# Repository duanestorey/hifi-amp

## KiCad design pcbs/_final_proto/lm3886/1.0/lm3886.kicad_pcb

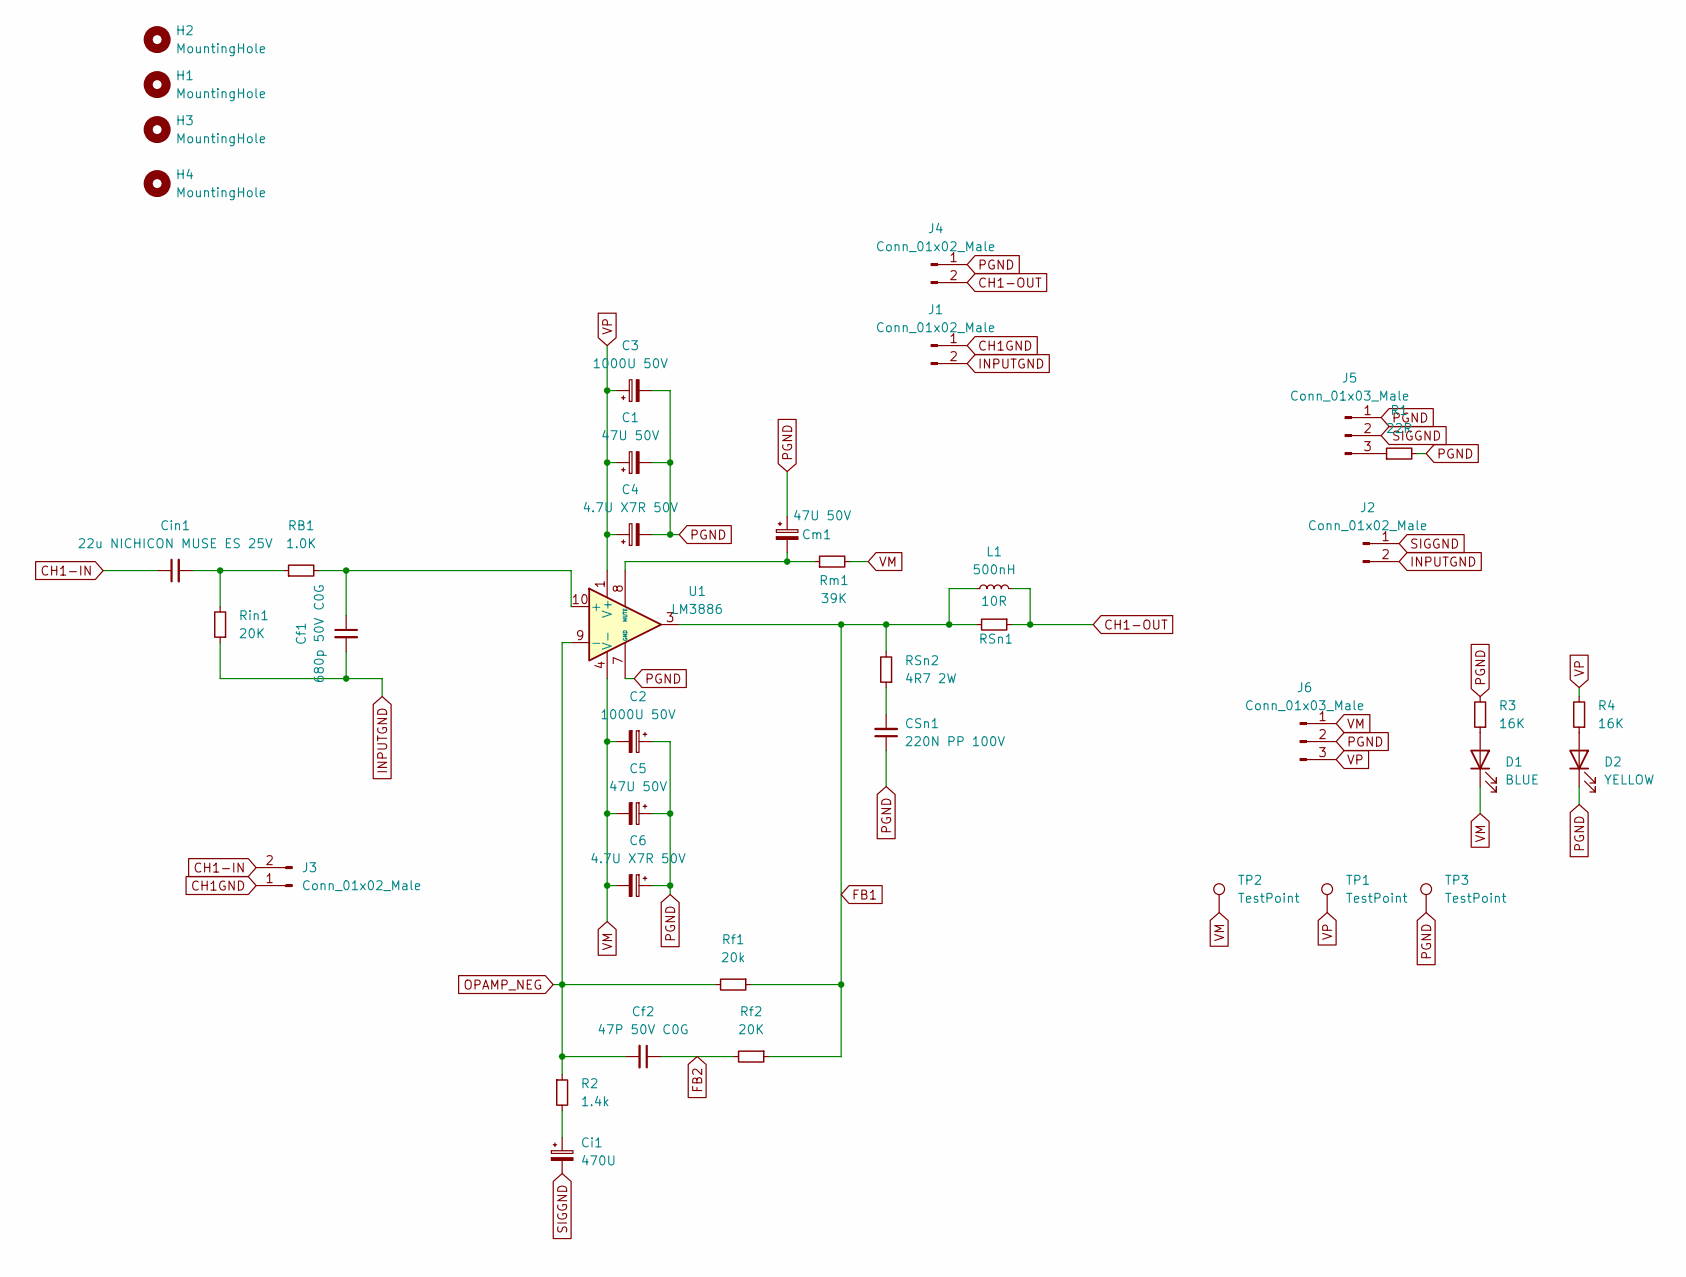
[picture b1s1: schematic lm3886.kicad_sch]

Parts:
C1, C5: 47U 50V; CP_Radial_D6.3mm_P2.50mm
C2, C3: 1000U 50V; CP_Radial_D12.5mm_P5.00mm
C4, C6: 4.7U X7R 50V; C_1206_3216Metric_Pad1.33x1.80mm_HandSolder; Mouser 80-C1206X475J5RACTU
CSn1: 220N PP 100V; C_Rect_L18.0mm_W7.0mm_P15.00mm_FKS3_FKP3; Mouser 505-MKP1D032204D00JB
Cf1: 680p 50V C0G; C_1206_3216Metric_Pad1.33x1.80mm_HandSolder; Mouser 603-CC126GRNPO9BN681
Cf2: 47P 50V C0G; C_1206_3216Metric_Pad1.33x1.80mm_HandSolder; Mouser 791-1206N470F500CT
Ci1: 470U; CP_Radial_D12.5mm_P5.00mm
Cin1: 22u NICHICON MUSE ES 25V; C_Radial_D6.3mm_H5.0mm_P2.50mm
Cm1: 47U 50V; CP_Radial_D6.3mm_P2.50mm
D1: BLUE; LED_0805_2012Metric_Pad1.15x1.40mm_HandSolder
D2: YELLOW; LED_0805_2012Metric_Pad1.15x1.40mm_HandSolder
H1, H2, H3, H4: MountingHole; MountingHole_3.2mm_M3_DIN965_Pad_TopOnly
J1, J2: Conn_01x02_Male; PinHeader_1x02_P2.54mm_Vertical
J3: Conn_01x02_Male; TerminalBlock_Phoenix_PT-1,5-2-3.5-H_1x02_P3.50mm_Horizontal
J4: Conn_01x02_Male; TerminalBlock_Phoenix_PT-1,5-2-5.0-H_1x02_P5.00mm_Horizontal
J5: Conn_01x03_Male; PinHeader_1x03_P2.54mm_Vertical
J6: Conn_01x03_Male; TerminalBlock_Phoenix_PT-1,5-3-5.0-H_1x03_P5.00mm_Horizontal
L1: 500nH; 500nH Inductor Aliexpress Air Gap
R1: 22R; R_1206_3216Metric_Pad1.30x1.75mm_HandSolder
R2: 1.4k; R_1206_3216Metric_Pad1.30x1.75mm_HandSolder; Mouser 603-RT1206FRE07750RL
R3, R4: 16K; R_0805_2012Metric_Pad1.20x1.40mm_HandSolder
RB1: 1.0K; R_1206_3216Metric_Pad1.30x1.75mm_HandSolder; Mouser 603-RT1206FRE131KL
RSn1: 10R; R_4020_10251Metric_Pad1.65x5.30mm_HandSolder; Mouser 279-355010RJT
RSn2: 4R7 2W; R_2512_6332Metric_Pad1.40x3.35mm_HandSolder; Mouser 603-RC2512JK-7W4R7
Rf1: 20k; R_1206_3216Metric_Pad1.30x1.75mm_HandSolder; Mouser 603-RT1206FRD0720KL
Rf2: 20K; R_1206_3216Metric_Pad1.30x1.75mm_HandSolder; Mouser 603-RT1206FRD0720KL
Rin1: 20K; R_1206_3216Metric_Pad1.30x1.75mm_HandSolder; Mouser 603-RT1206FRD0720KL
Rm1: 39K; R_1206_3216Metric_Pad1.30x1.75mm_HandSolder; Mouser 603-RC1206JR-0739KL
TP1, TP2, TP3: TestPoint; TestPoint_THTPad_1.5x1.5mm_Drill0.7mm
U1: LM3886; TO-220-11_P3.4x5.08mm_StaggerOdd_Lead4.85mm_Vertical

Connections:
CH1-IN: Cin1.1, J3.2
CH1-OUT: J4.2, L1.2, RSn1.1
CH1GND: J1.1, J3.1
FB1: L1.1, RSn1.2, RSn2.2, Rf1.1, Rf2.1, U1.3
FB2: Cf2.1, Rf2.2
INPUTGND: Cf1.2, J1.2, J2.2, Rin1.1
unnamed: CSn1.2, RSn2.1
unnamed: Ci1.1, R2.2
unnamed: Cin1.2, RB1.1, Rin1.2
unnamed: D1.2 (A), R3.1
unnamed: D2.2 (A), R4.1
unnamed: J5.3, R1.1
unnamed: Cf1.1, RB1.2, U1.10 (+)
unnamed: Cm1.2, Rm1.1, U1.8 (MUTE)
OPAMP_NEG: Cf2.2, R2.1, Rf1.2, U1.9 (-)
PGND: C1.2, C2.1, C3.2, C4.2, C5.1, C6.1, CSn1.1, Cm1.1, D2.1 (K), J4.1, J5.1, J6.2, R1.2, R3.2, TP3.1, U1.7 (GND)
SIGGND: Ci1.2, J2.1, J5.2
VM: C2.2, C5.2, C6.2, D1.1 (K), J6.1, Rm1.2, TP2.1, U1.4 (V-)
VP: C1.1, C3.1, C4.1, J6.3, R4.2, TP1.1, U1.1 (V+), U1.5 (V+)

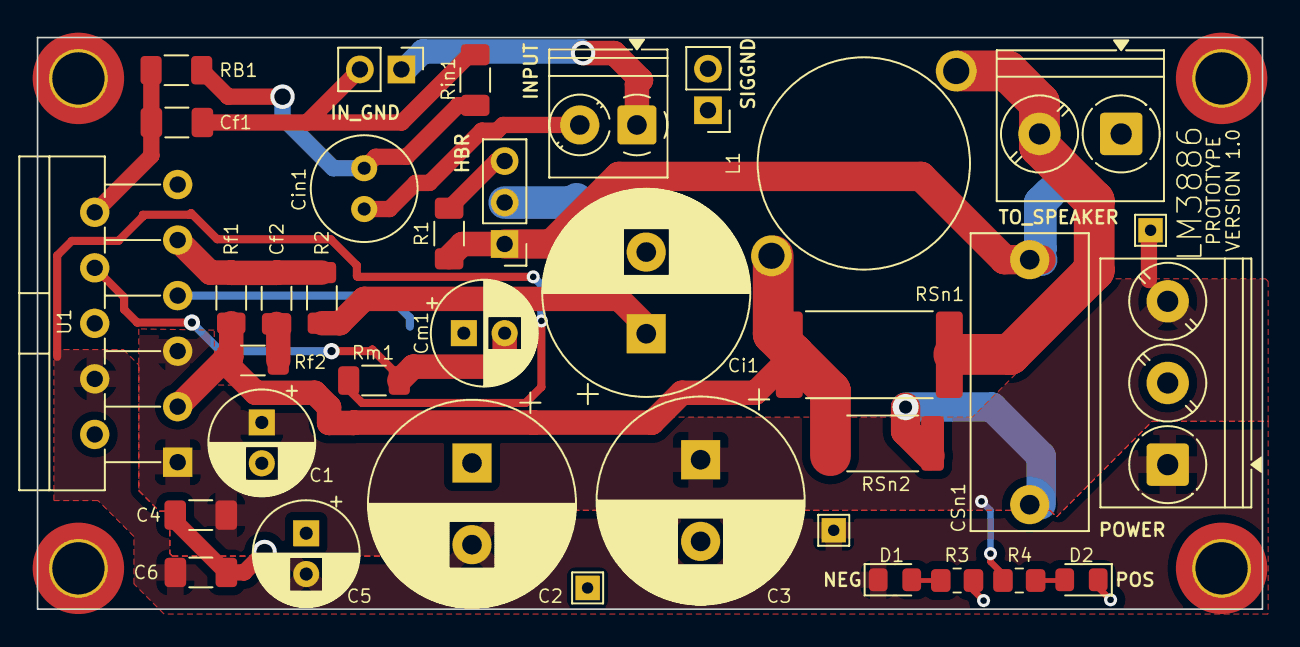
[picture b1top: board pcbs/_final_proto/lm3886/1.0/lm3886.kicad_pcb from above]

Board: 2 copper layers, 75.0 x 35.0 mm, 40 parts (0 on the bottom side), 19 nets.

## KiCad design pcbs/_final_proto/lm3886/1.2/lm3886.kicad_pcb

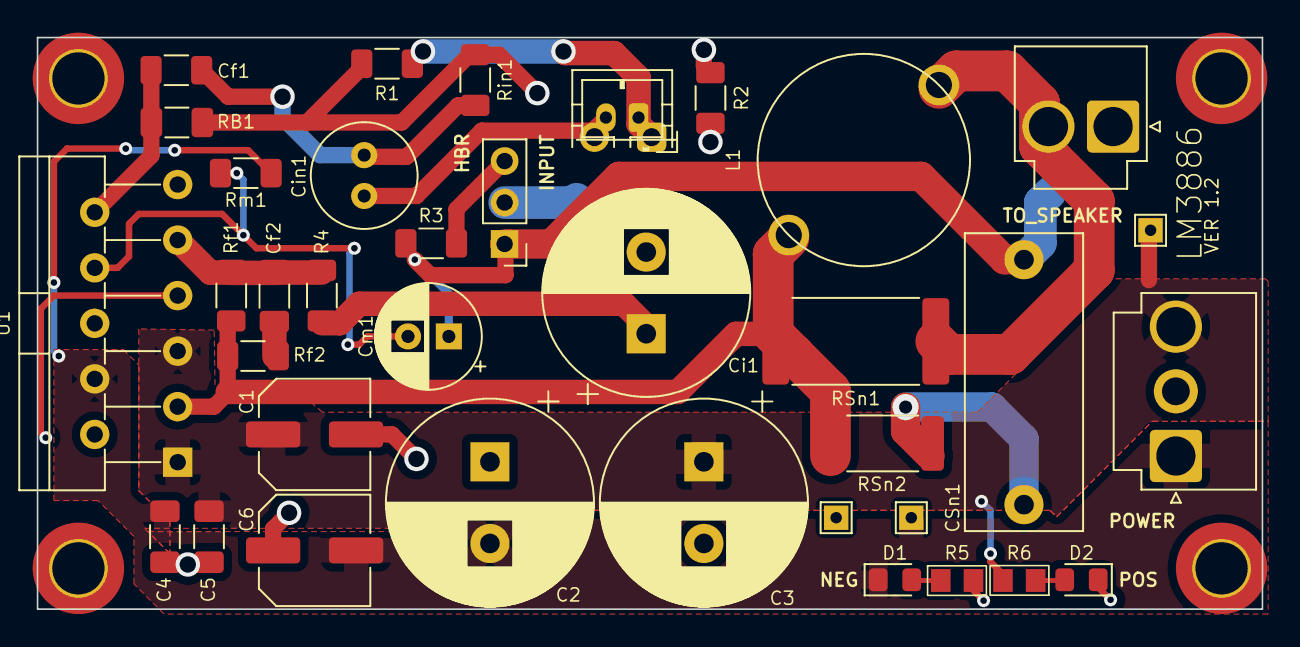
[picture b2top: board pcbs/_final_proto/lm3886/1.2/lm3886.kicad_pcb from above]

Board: 2 copper layers, 75.0 x 35.0 mm, 40 parts (0 on the bottom side), 19 nets.

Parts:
C1, C6: 22u 50V; C_Elec_6.3x5.4
C2, C3: 1000U 50V; CP_Radial_D12.5mm_P5.00mm
C4, C5: 4.7U X7R 50V; C_1206_3216Metric_Pad1.33x1.80mm_HandSolder
CSn1: 220N PP 100V; C_Rect_L18.0mm_W7.0mm_P15.00mm_FKS3_FKP3
Cf1: 680p 50V C0G; C_1206_3216Metric_Pad1.33x1.80mm_HandSolder
Cf2: 47P 50V C0G; C_1206_3216Metric_Pad1.33x1.80mm_HandSolder
Ci1: 470U; CP_Radial_D12.5mm_P5.00mm
Cin1: 22u NICHICON MUSE ES 25V; C_Radial_D6.3mm_H5.0mm_P2.50mm
Cm1: 47U 50V; CP_Radial_D6.3mm_P2.50mm
D1: BLUE; LED_0805_2012Metric_Pad1.15x1.40mm_HandSolder
D2: YELLOW; LED_0805_2012Metric_Pad1.15x1.40mm_HandSolder
H1, H2, H3, H4: MountingHole; MountingHole_3.2mm_M3_DIN965_Pad_TopOnly
J1: Conn_01x02_Male; JST_PH_B2B-PH-K_1x02_P2.00mm_Vertical_Duane
J2: Conn_01x02_Male; JST_VH_B2P-VH-B_1x02_P3.96mm_Vertical_Duane
J3: Conn_01x03_Male; PinHeader_1x03_P2.54mm_Vertical
J4: Conn_01x03_Male; JST_VH_B3P-VH-B_1x03_P3.96mm_Vertical_Duane
L1: 700nH; 500nH Inductor Aliexpress Air Gap
R1, R2: 0R; R_1206_3216Metric_Pad1.30x1.75mm_HandSolder
R3: 22R; R_1206_3216Metric_Pad1.30x1.75mm_HandSolder
R4: 1.4k; R_1206_3216Metric_Pad1.30x1.75mm_HandSolder
R5, R6: 16K; R_0805_2012Metric_Pad1.20x1.40mm_HandSolder_Duane
RB1: 1.0K; R_1206_3216Metric_Pad1.30x1.75mm_HandSolder
RSn1: 10R; R_4020_10251Metric_Pad1.65x5.30mm_HandSolder
RSn2: 4R7 2W; R_2512_6332Metric_Pad1.40x3.35mm_HandSolder
Rf1: 20k; R_1206_3216Metric_Pad1.30x1.75mm_HandSolder
Rf2: 20K; R_1206_3216Metric_Pad1.30x1.75mm_HandSolder
Rin1: 20K; R_1206_3216Metric_Pad1.30x1.75mm_HandSolder
Rm1: 39K; R_1206_3216Metric_Pad1.30x1.75mm_HandSolder
TP1, TP2, TP3: TestPoint; TestPoint_THTPad_1.5x1.5mm_Drill0.7mm
U1: LM3886

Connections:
CH1-IN: Cin1.1, J1.2
CH1-OUT: J2.2, L1.2, RSn1.1
CH1GND: J1.1, R1.1
INPUTGND: Cf1.2, R1.2, R2.1, Rin1.1
MUTE: Cm1.2, Rm1.1, U1.8 (MUTE)
NEG: C2.2, C4.2, C6.2, D1.1 (K), J4.1, Rm1.2, TP3.1, U1.4 (V-)
unnamed: CSn1.2, RSn2.1
unnamed: Cf2.1, Rf2.2
unnamed: Ci1.1, R4.2
unnamed: Cin1.2, RB1.1, Rin1.2
unnamed: D1.2 (A), R5.1
unnamed: D2.2 (A), R6.1
unnamed: J3.3, R3.1
unnamed: L1.1, RSn1.2, RSn2.2, Rf1.1, Rf2.1, U1.3
unnamed: Cf1.1, RB1.2, U1.10 (+)
OPAMP_NEG: Cf2.2, R4.1, Rf1.2, U1.9 (-)
PGND: C1.2, C2.1, C3.2, C4.1, C5.2, C6.1, CSn1.1, Cm1.1, D2.1 (K), J2.1, J3.1, J4.2, R3.2, R5.2, TP2.1, U1.7 (GND)
POS: C1.1, C3.1, C5.1, J4.3, R6.2, TP1.1, U1.1 (V+), U1.5 (V+)
SIGGND: Ci1.2, J3.2, R2.2

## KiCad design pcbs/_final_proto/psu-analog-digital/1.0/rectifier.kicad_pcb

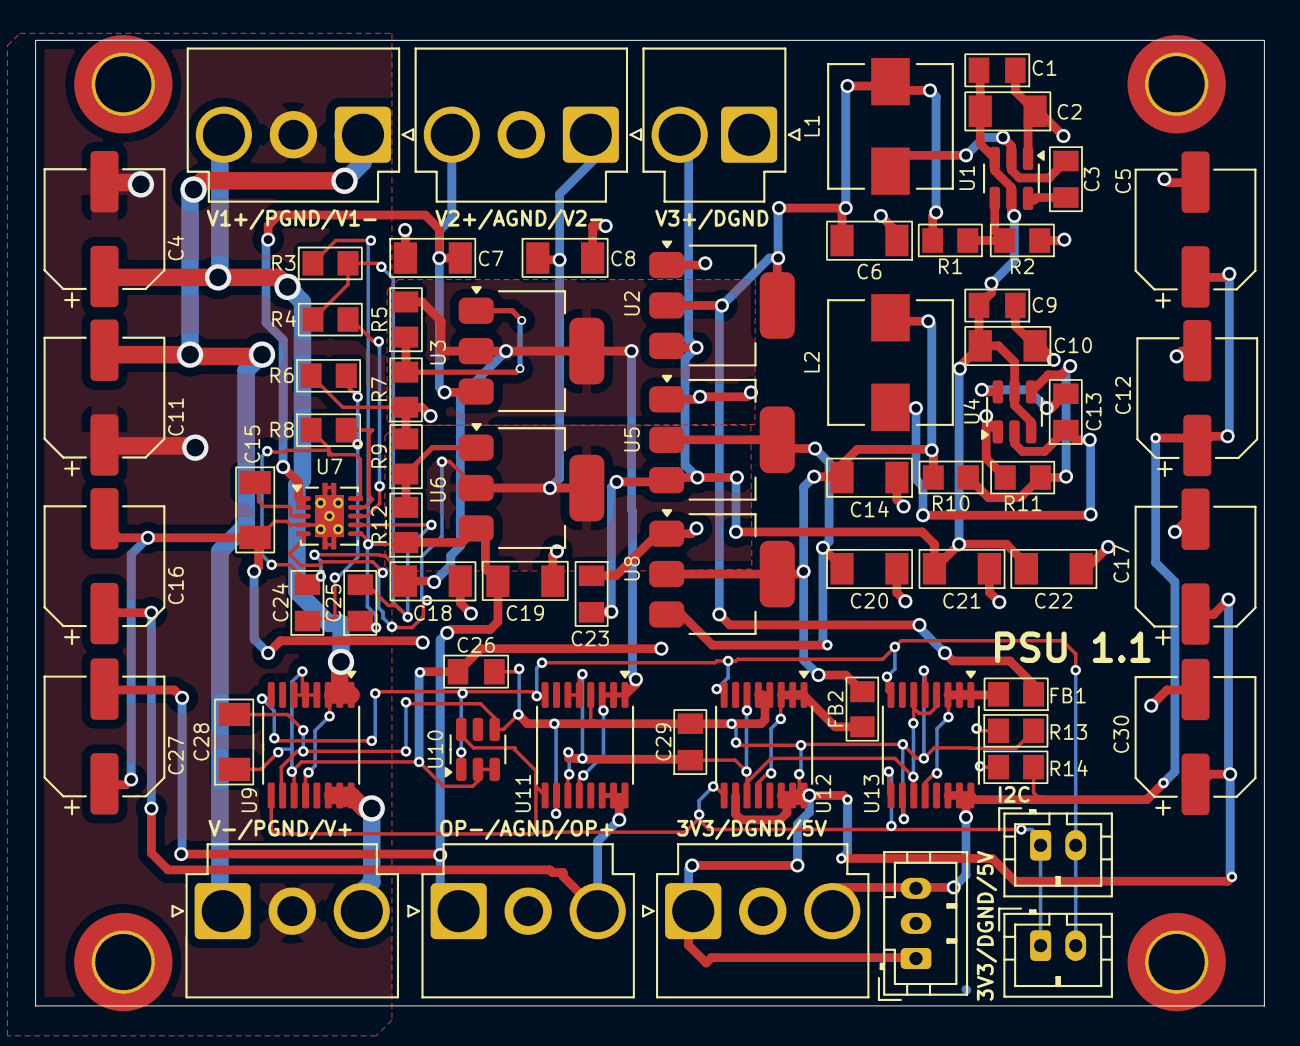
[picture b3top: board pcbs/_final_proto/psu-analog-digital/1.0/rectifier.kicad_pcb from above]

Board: 2 copper layers, 70.0 x 55.0 mm, 74 parts (0 on the bottom side), 33 nets.

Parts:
C1, C3, C9, C13, C23, C26, C29: 0.1u; C_0805_2012Metric_Pad1.18x1.45mm_HandSolder_Duane
C2, C6, C7, C8, C10, C14, C15, C18, C19, C20, C21, C22, C28: 10u; C_1206_3216Metric_Pad1.33x1.80mm_HandSolder_Duane
C4, C5, C11, C12, C16, C17, C27, C30: 470u; CP_Elec_6.3x7.7
C24, C25: 0.01u; C_0805_2012Metric_Pad1.18x1.45mm_HandSolder_Duane
FB1, FB2: FerriteBead_Small; R_0805_2012Metric_Pad1.20x1.40mm_HandSolder_Duane
H1, H2, H3, H4: MountingHole; MountingHole_3.2mm_M3_DIN965_Pad_TopBottom
J1, J2, J5, J6, J7: Conn_01x03; JST_VH_B3P-VH-B_1x03_P3.96mm_Vertical_Duane
J3: Conn_01x02; JST_VH_B2P-VH-B_1x02_P3.96mm_Vertical_Duane
J4, J8: Conn_01x02; JST_PH_B2B-PH-K_1x02_P2.00mm_Vertical
J9: Conn_01x03; JST_PH_B3B-PH-K_1x03_P2.00mm_Vertical
L1: 3.3u; L_Wuerth_HCI-7030
L2: 2.2u; L_Wuerth_HCI-7030
R1, R3, R5, R7, R9, R10, R12: 100k; R_0805_2012Metric_Pad1.20x1.40mm_HandSolder_Duane
R2: 13.7k; R_0805_2012Metric_Pad1.20x1.40mm_HandSolder_Duane
R4, R6, R13, R14: 10k; R_0805_2012Metric_Pad1.20x1.40mm_HandSolder_Duane
R8: 90.9k; R_0805_2012Metric_Pad1.20x1.40mm_HandSolder_Duane
R11: 22.1k; R_0805_2012Metric_Pad1.20x1.40mm_HandSolder_Duane
U1, U4: LMR51430; SOT-23-6
U2, U5: TLV76150DCY; SOT-223-3_TabPin2
U3: LM317_SOT-223; SOT-223-3_TabPin2
U6: LM337_SOT223; SOT-223-3_TabPin2
U7: TPS7A39; Texas_S-PVSON-N10_ThermalVias
U8: TLV76133DCY; SOT-223-3_TabPin2
U9, U11, U12, U13: INA260; TSSOP-16_4.4x5mm_P0.65mm
U10: TMP100; SOT-23-6

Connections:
3V3: C14.2, FB2.1, L2.2, R10.2, U8.2 (VO)
3V3_OUT: C17.1, C26.2, C28.2, C29.2, C30.1, J7.1, J9.1, R13.2, U9.10 (VS), U10.4 (V+), U11.4 (A1), U11.10 (VS), U12.4 (A1), U12.5 (A0), U12.10 (VS), U12.14 (IN-), U12.15 (IN-), U12.16 (IN-), U13.5 (A0), U13.10 (VS)
5V: C6.2, FB1.1, L1.2, R1.2, U2.2 (VO)
5V_OUT: C5.1, C12.1, J7.3, J9.3, R14.2, U13.14 (IN-), U13.15 (IN-), U13.16 (IN-)
5V_TEMP: C20.2, U5.2 (VO), U8.3 (VI)
AGND: C7.1, C8.2, C15.2, C16.2, C18.1, C19.2, C27.1, J2.2, J6.2, R6.1, R7.1, R9.2, U7.4 (GND), U7.11 (GND)
DGND: C1.1, C2.1, C5.2, C6.1, C9.1, C10.1, C12.2, C14.1, C17.2, C20.1, C21.1, C22.1, C23.1, C26.1, C28.1, C29.1, C30.2, J3.1, J7.2, J9.2, R2.1, R11.1, R13.1, R14.1, U1.1 (GND), U2.1 (GND), U4.1 (GND), U5.1 (GND), U8.1 (GND), U9.4 (A1), U9.5 (A0), U9.6 (GND), U9.11 (GND), U10.2 (GND), U10.3 (ADD1), U11.5 (A0), U11.6 (GND), U11.11 (GND), U12.6 (GND), U12.11 (GND), U13.4 (A1), U13.6 (GND), U13.11 (GND)
unnamed: C3.2, U1.6 (CB)
unnamed: R1.1, R2.2, U1.4 (FB)
unnamed: C3.1, L1.1, U1.2 (SW)
unnamed: R5.1, R7.2, U3.1 (ADJ)
unnamed: C13.2, U4.6 (CB)
unnamed: R10.1, R11.2, U4.4 (FB)
unnamed: C13.1, L2.1, U4.2 (SW)
unnamed: R9.1, R12.2, U6.1 (ADJ)
unnamed: R4.2, U7.8 (BUF)
unnamed: C25.2, R3.2, R4.1, U7.7 (FBN)
unnamed: C24.1, R6.2, R8.2, U7.9 (FBP)
unnamed: C15.1, U7.3 (NR/SS)
unnamed: FB2.2, U12.1 (IN+), U12.2 (IN+), U12.3 (IN+), U12.12 (VBUS)
unnamed: FB1.2, U13.1 (IN+), U13.2 (IN+), U13.3 (IN+), U13.12 (VBUS)
OPAMP+: C18.2, C24.2, R5.2, R8.1, U3.2 (VO), U7.10 (OUTP), U11.1 (IN+), U11.2 (IN+), U11.3 (IN+), U11.12 (VBUS)
OPAMP+_OUT: C16.1, J6.3, U11.14 (IN-), U11.15 (IN-), U11.16 (IN-)
OPAMP-: C19.1, C25.1, C27.2, J6.1, R3.1, R12.1, U6.3 (VO), U7.6 (OUTN)
PGND: C4.2, C11.1, J1.2, J5.2
SCL: J4.1, J8.1, U9.9 (SCL), U10.6 (SDA), U11.9 (SCL), U12.9 (SCL), U13.9 (SCL)
SDA: J4.2, J8.2, U9.8 (SDA), U10.1 (SCL), U11.8 (SDA), U12.8 (SDA), U13.8 (SDA)
V2+FUSED: C7.2, J2.3, U3.3 (VI), U7.1 (INP), U7.2 (EN)
V2-FUSED: C8.1, J2.1, U6.2 (VI), U7.5 (INN)
V3+FUSED: C1.2, C2.2, C9.2, C10.2, C21.2, C22.2, C23.2, J3.2, U1.3 (VIN), U1.5 (EN), U2.3 (VI), U4.3 (VIN), U4.5 (EN), U5.3 (VI)
V+FUSED: C4.1, J1.3, U9.1 (IN+), U9.2 (IN+), U9.3 (IN+), U9.12 (VBUS)
V+FUSED_OUT: J5.3, U9.14 (IN-), U9.15 (IN-), U9.16 (IN-)
V-FUSED: C11.2, J1.1, J5.1

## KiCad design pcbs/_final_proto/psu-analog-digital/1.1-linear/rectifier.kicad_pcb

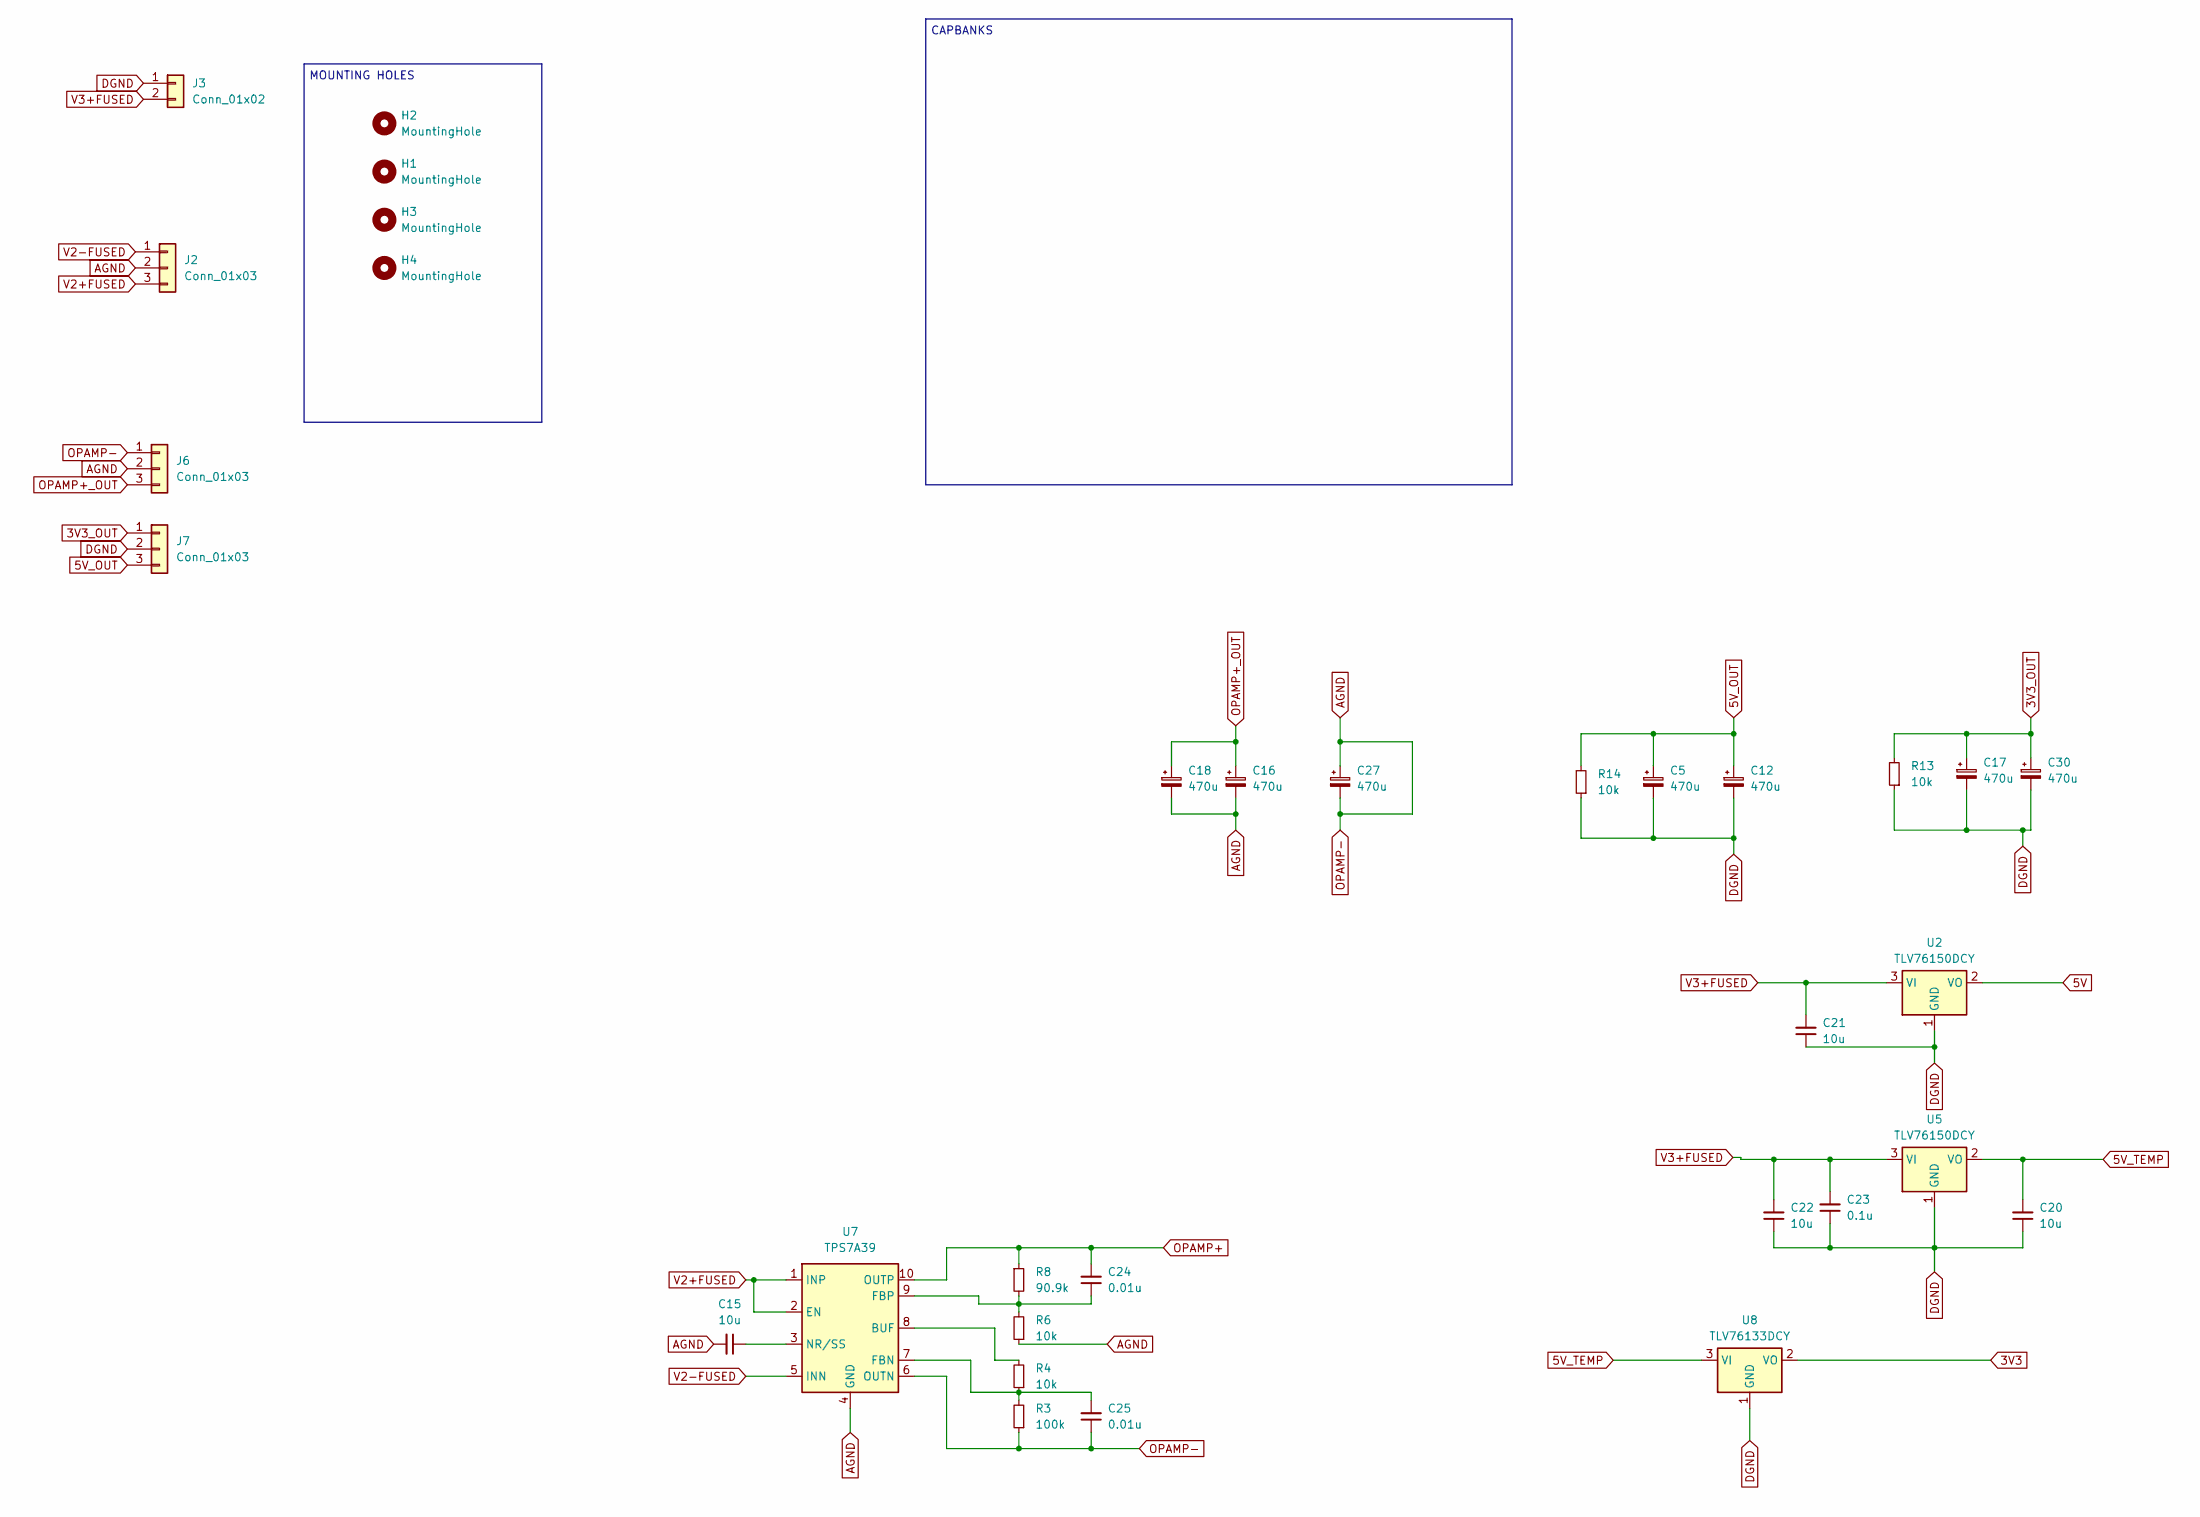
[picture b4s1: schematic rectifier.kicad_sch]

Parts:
C5, C12, C16, C17, C18, C27, C30: 470u; CP_Elec_6.3x7.7
C15, C20, C21, C22: 10u; C_1206_3216Metric_Pad1.33x1.80mm_HandSolder_Duane
C23: 0.1u; C_0805_2012Metric_Pad1.18x1.45mm_HandSolder_Duane
C24, C25: 0.01u; C_0805_2012Metric_Pad1.18x1.45mm_HandSolder_Duane
H1, H2, H3, H4: MountingHole; MountingHole_3.2mm_M3_DIN965_Pad_TopBottom
J2, J6, J7: Conn_01x03; JST_VH_B3P-VH-B_1x03_P3.96mm_Vertical_Duane
J3: Conn_01x02; JST_VH_B2P-VH-B_1x02_P3.96mm_Vertical_Duane
R3: 100k; R_0805_2012Metric_Pad1.20x1.40mm_HandSolder_Duane
R4, R6, R13, R14: 10k; R_0805_2012Metric_Pad1.20x1.40mm_HandSolder_Duane
R8: 90.9k; R_0805_2012Metric_Pad1.20x1.40mm_HandSolder_Duane
U2, U5: TLV76150DCY; SOT-223-3_TabPin2
U7: TPS7A39; Texas_S-PVSON-N10_ThermalVias
U8: TLV76133DCY; SOT-223-3_TabPin2

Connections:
3V3: U8.2 (VO)
3V3_OUT: C17.1, C30.1, J7.1, R13.2
5V: U2.2 (VO)
5V_OUT: C5.1, C12.1, J7.3, R14.2
5V_TEMP: C20.2, U5.2 (VO), U8.3 (VI)
AGND: C15.2, C16.2, C18.2, C25.1, C27.1, C27.2, J2.2, J6.1, J6.2, R3.1, R6.1, U7.4 (GND), U7.6 (OUTN), U7.11 (GND)
DGND: C5.2, C12.2, C17.2, C20.1, C21.1, C22.1, C23.1, C30.2, J3.1, J7.2, R13.1, R14.1, U2.1 (GND), U5.1 (GND), U8.1 (GND)
unnamed: R4.2, U7.8 (BUF)
unnamed: C25.2, R3.2, R4.1, U7.7 (FBN)
unnamed: C24.1, R6.2, R8.2, U7.9 (FBP)
unnamed: C15.1, U7.3 (NR/SS)
OPAMP+: C24.2, R8.1, U7.10 (OUTP)
OPAMP+_OUT: C16.1, C18.1, J6.3
V2+FUSED: J2.3, U7.1 (INP), U7.2 (EN)
V2-FUSED: J2.1, U7.5 (INN)
V3+FUSED: C21.2, C22.2, C23.2, J3.2, U2.3 (VI), U5.3 (VI)

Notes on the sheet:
MOUNTING HOLES
CAPBANKS

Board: 2 copper layers, 32 parts (0 on the bottom side), 14 nets, no tracks yet.

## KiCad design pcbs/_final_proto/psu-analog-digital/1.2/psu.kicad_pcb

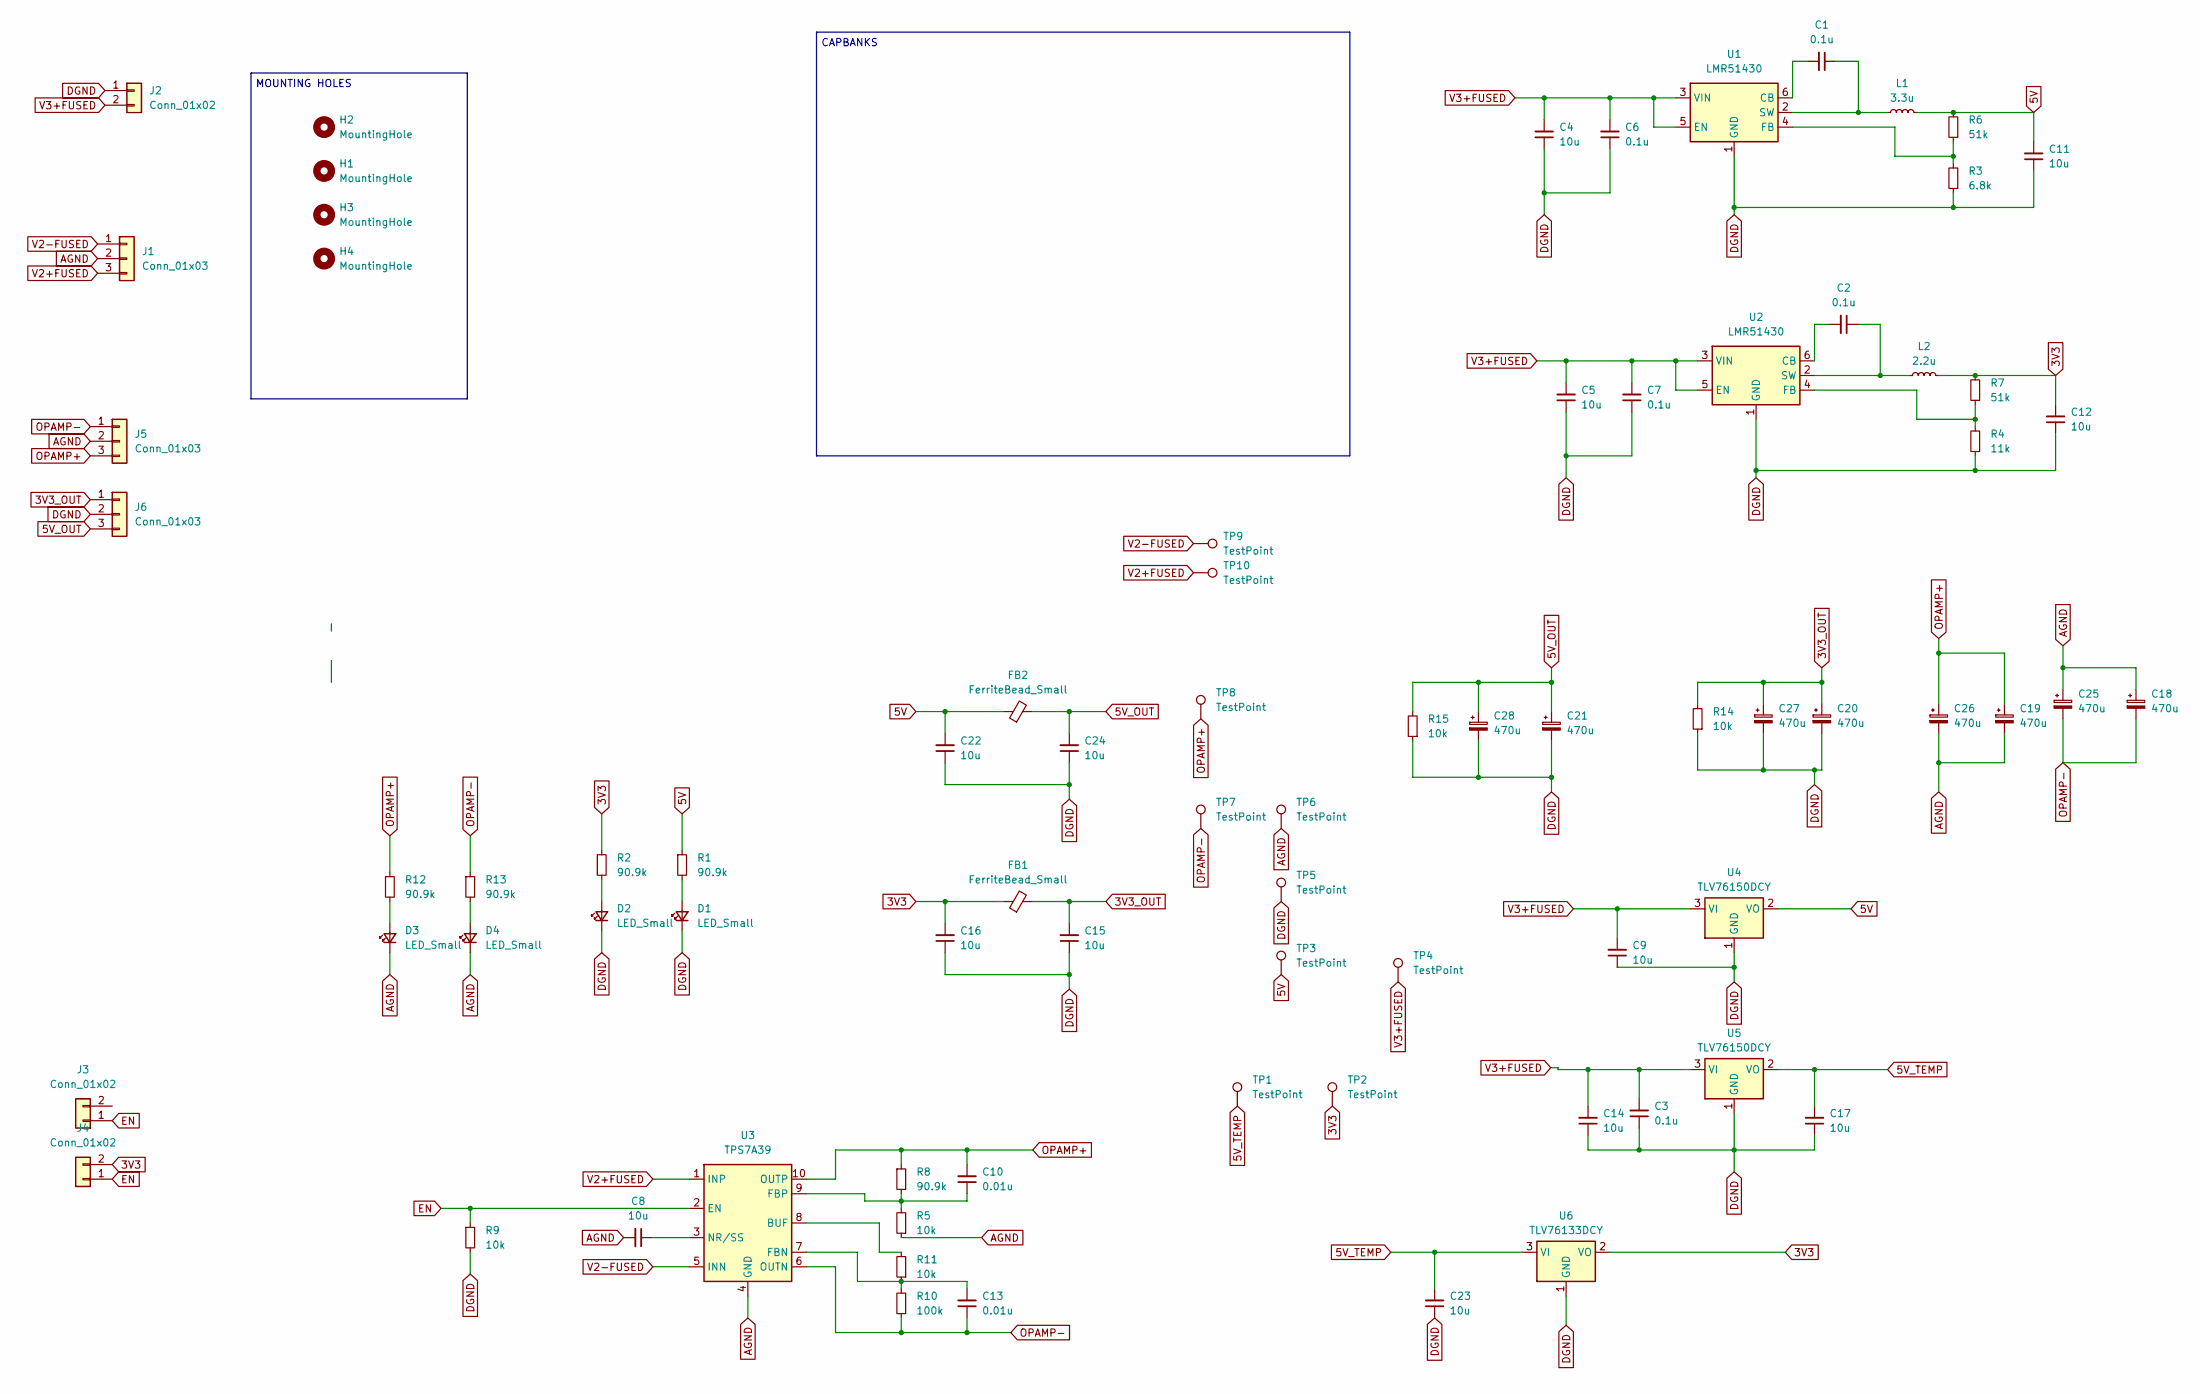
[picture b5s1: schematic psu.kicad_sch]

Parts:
C1, C2, C3, C6, C7: 0.1u; C_0805_2012Metric_Pad1.18x1.45mm_HandSolder_Duane
C4, C5, C8, C9, C11, C12, C14, C15, C16, C17, C22, C23, C24: 10u; C_1206_3216Metric_Pad1.33x1.80mm_HandSolder_Duane
C10, C13: 0.01u; C_0805_2012Metric_Pad1.18x1.45mm_HandSolder_Duane
C18, C19, C20, C21, C25, C26, C27, C28: 470u; CP_Elec_6.3x7.7
D1, D2, D3, D4: LED_Small; LED_0805_2012Metric_Pad_HandSolder_Duane
FB1, FB2: FerriteBead_Small; R_0805_2012Metric_Pad1.20x1.40mm_HandSolder_Duane
H1, H2, H3, H4: MountingHole; MountingHole_3.2mm_M3_DIN965_Pad_TopBottom
J1, J5, J6: Conn_01x03; JST_VH_B3P-VH-B_1x03_P3.96mm_Vertical_Duane
J2: Conn_01x02; JST_VH_B2P-VH-B_1x02_P3.96mm_Vertical_Duane
J3: Conn_01x02; JST_PH_B2B-PH-K_1x02_P2.00mm_Vertical
J4: Conn_01x02; PinHeader_1x02_P2.54mm_Vertical
L1: 3.3u; L_Wuerth_HCI-7030
L2: 2.2u; L_Wuerth_HCI-7030
R1, R2, R8, R12, R13: 90.9k; R_0805_2012Metric_Pad1.20x1.40mm_HandSolder_Duane
R3: 6.8k; R_0805_2012Metric_Pad1.20x1.40mm_HandSolder_Duane
R4: 11k; R_0805_2012Metric_Pad1.20x1.40mm_HandSolder_Duane
R5, R9, R11, R14, R15: 10k; R_0805_2012Metric_Pad1.20x1.40mm_HandSolder_Duane
R6, R7: 51k; R_0805_2012Metric_Pad1.20x1.40mm_HandSolder_Duane
R10: 100k; R_0805_2012Metric_Pad1.20x1.40mm_HandSolder_Duane
TP1, TP2, TP3, TP4, TP5, TP6, TP7, TP8, TP9, TP10: TestPoint; TestPoint_THTPad_2.5x2.5mm_Drill1.2mm
U1, U2: LMR51430; SOT-23-6
U3: TPS7A39; Texas_S-PVSON-N10_ThermalVias
U4, U5: TLV76150DCY; SOT-223-3_TabPin2
U6: TLV76133DCY; SOT-223-3_TabPin2

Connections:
3V3: C12.2, C16.2, FB1.1, J4.2, L2.2, R2.1, R7.2, TP2.1, U6.2 (VO)
3V3_OUT: C15.2, C20.1, C27.1, FB1.2, J6.1, R14.2
5V: C11.2, C22.2, FB2.1, L1.2, R1.1, R6.2, TP3.1, U4.2 (VO)
5V_OUT: C21.1, C24.2, C28.1, FB2.2, J6.3, R15.2
5V_TEMP: C17.2, C23.2, TP1.1, U5.2 (VO), U6.3 (VI)
AGND: C8.2, C18.1, C19.2, C25.1, C26.2, D3.1 (K), D4.1 (K), J1.2, J5.2, R5.1, TP6.1, U3.4 (GND), U3.11 (GND)
DGND: C3.1, C4.1, C5.1, C6.1, C7.1, C9.1, C11.1, C12.1, C14.1, C15.1, C16.1, C17.1, C20.2, C21.2, C22.1, C23.1, C24.1, C27.2, C28.2, D1.1 (K), D2.1 (K), J2.1, J6.2, R3.1, R4.1, R9.2, R14.1, R15.1, TP5.1, U1.1 (GND), U2.1 (GND), U4.1 (GND), U5.1 (GND), U6.1 (GND)
EN: J3.1, J4.1, R9.1, U3.2 (EN)
unnamed: D1.2 (A), R1.2
unnamed: D2.2 (A), R2.2
unnamed: D3.2 (A), R12.2
unnamed: D4.2 (A), R13.2
unnamed: C1.2, U1.6 (CB)
unnamed: R3.2, R6.1, U1.4 (FB)
unnamed: C1.1, L1.1, U1.2 (SW)
unnamed: C2.2, U2.6 (CB)
unnamed: R4.2, R7.1, U2.4 (FB)
unnamed: C2.1, L2.1, U2.2 (SW)
unnamed: R11.2, U3.8 (BUF)
unnamed: C13.2, R10.2, R11.1, U3.7 (FBN)
unnamed: C10.1, R5.2, R8.2, U3.9 (FBP)
unnamed: C8.1, U3.3 (NR/SS)
OPAMP+: C10.2, C19.1, C26.1, J5.3, R8.1, R12.1, TP8.1, U3.10 (OUTP)
OPAMP-: C13.1, C18.2, C25.2, J5.1, R10.1, R13.1, TP7.1, U3.6 (OUTN)
V2+FUSED: J1.3, TP10.1, U3.1 (INP)
V2-FUSED: J1.1, TP9.1, U3.5 (INN)
V3+FUSED: C3.2, C4.2, C5.2, C6.2, C7.2, C9.2, C14.2, J2.2, TP4.1, U1.3 (VIN), U1.5 (EN), U2.3 (VIN), U2.5 (EN), U4.3 (VI), U5.3 (VI)

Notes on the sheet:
MOUNTING HOLES
CAPBANKS

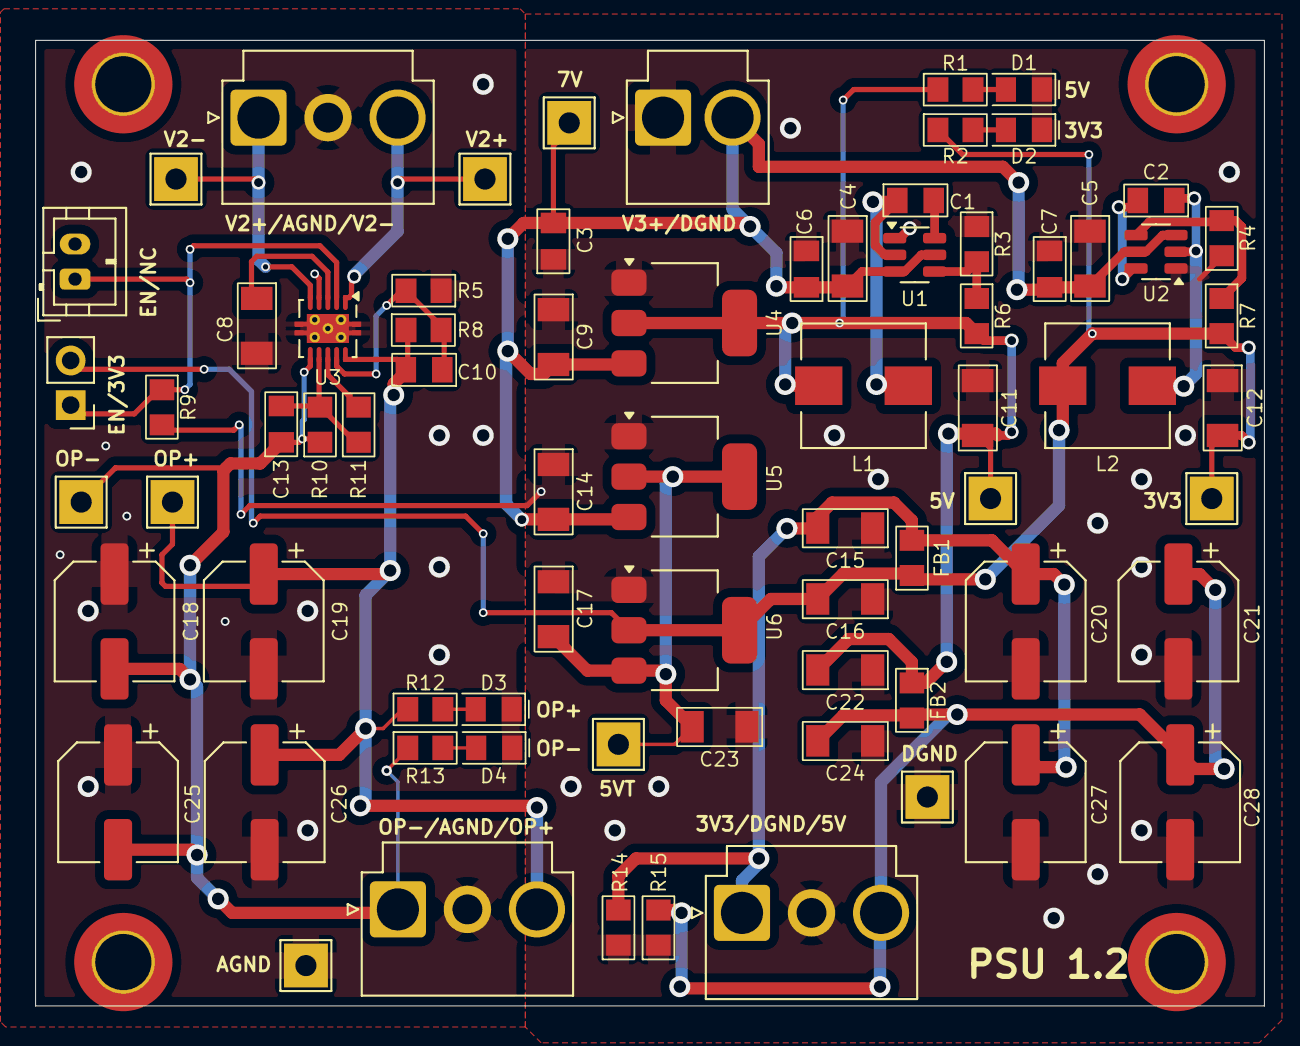
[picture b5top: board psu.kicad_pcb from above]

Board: 2 copper layers, 70.0 x 55.0 mm, 77 parts (0 on the bottom side), 27 nets.

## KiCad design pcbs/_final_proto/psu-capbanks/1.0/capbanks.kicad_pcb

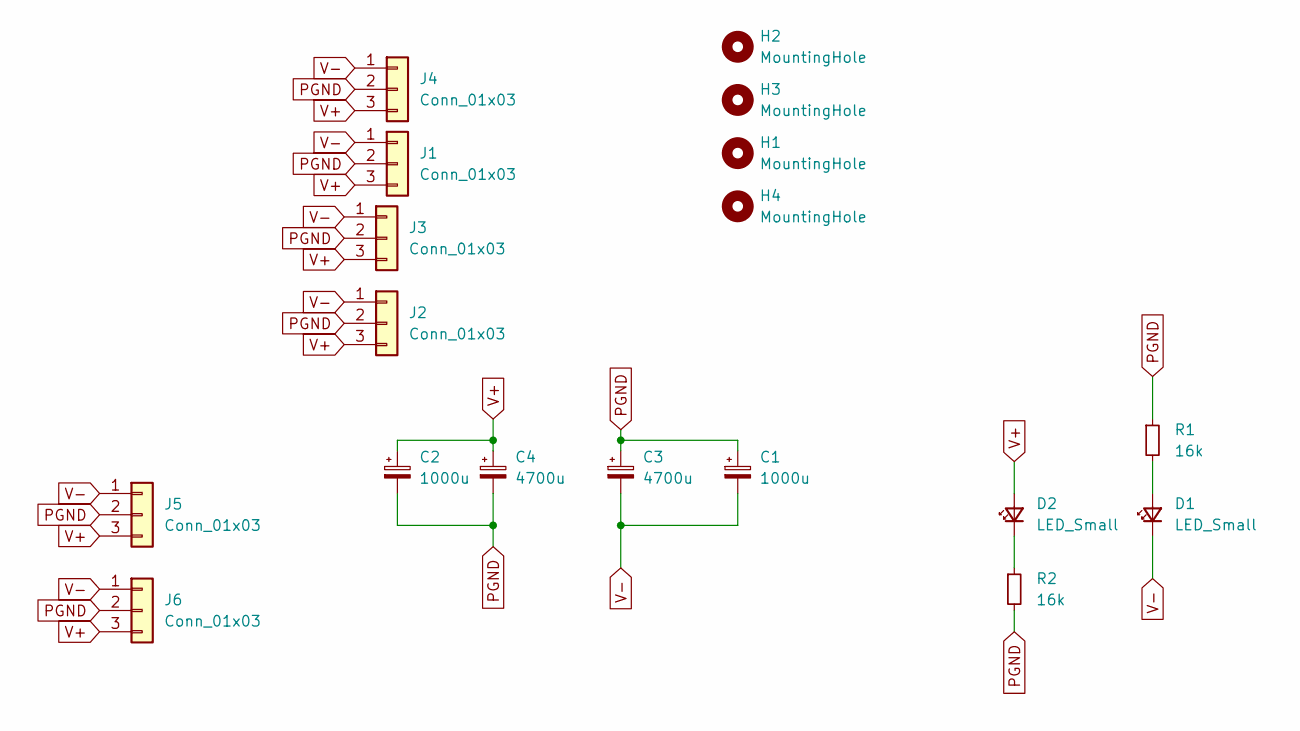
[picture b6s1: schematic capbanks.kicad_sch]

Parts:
C1, C2: 1000u; CP_Radial_D12.5mm_P5.00mm
C3, C4: 4700u; CP_Radial_D18.0mm_P7.50mm
D1, D2: LED_Small; LED_0805_2012Metric_Pad_HandSolder_Duane
H1, H2, H3, H4: MountingHole; MountingHole_3.2mm_M3_DIN965_Pad_TopBottom
J1, J2, J3, J4, J5, J6: Conn_01x03; TerminalBlock_Phoenix_PT-1,5-3-3.5-H_1x03_P3.50mm_Horizontal
R1, R2: 16k; R_0805_2012Metric_Pad1.20x1.40mm_HandSolder_Duane

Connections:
unnamed: D1.2 (A), R1.2
unnamed: D2.1 (K), R2.1
PGND: C1.1, C2.2, C3.1, C4.2, J1.2, J2.2, J3.2, J4.2, J5.2, J6.2, R1.1, R2.2
V+: C2.1, C4.1, D2.2 (A), J1.3, J2.3, J3.3, J4.3, J5.3, J6.3
V-: C1.2, C3.2, D1.1 (K), J1.1, J2.1, J3.1, J4.1, J5.1, J6.1
